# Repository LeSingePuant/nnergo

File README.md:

# nnErgo
nnErgo - NiceNano Ergonomic Keypad

This is a PCB I am using to learn KiCad design. It is designed simply for my needs. Any of my designs are able to be used, remixed, redone, produced commercially or otherwise as long as an attribution of my username "LeSingePuant" is given as credit (and a PM via Reddit or Twitter would be nice, although I rarely use Twitter). Thank you.

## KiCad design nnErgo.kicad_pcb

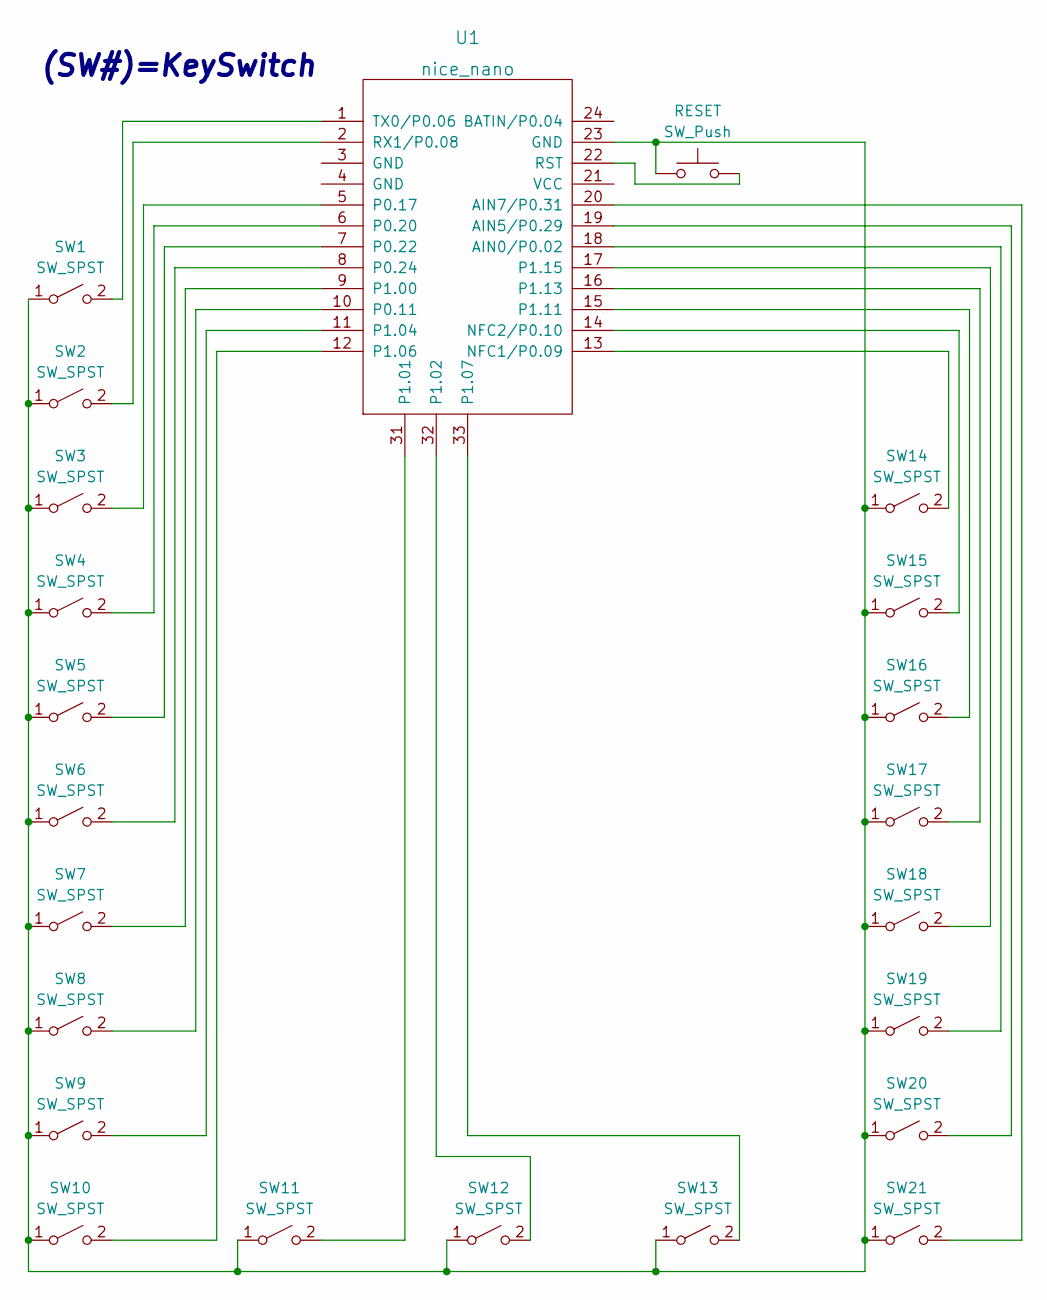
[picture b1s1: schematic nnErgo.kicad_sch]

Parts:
RESET: SW_Push; SW_PUSH_6mm
SW1, SW2, SW3, SW4, SW5, SW6, SW7, SW8, SW9, SW10, SW11, SW12, SW13, SW14, SW15, SW16, SW17, SW18, SW19, SW20, SW21: SW_SPST; Kailh_socket_MX
U1: nice_nano

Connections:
unnamed 0: RESET.1, SW1.1 (A), SW2.1 (A), SW3.1 (A), SW4.1 (A), SW5.1 (A), SW6.1 (A), SW7.1 (A), SW8.1 (A), SW9.1 (A), SW10.1 (A), SW11.1 (A), SW12.1 (A), SW13.1 (A), SW14.1 (A), SW15.1 (A), SW16.1 (A), SW17.1 (A), SW18.1 (A), SW19.1 (A), SW20.1 (A), SW21.1 (A), U1.23 (GND); also elsewhere on the board
unnamed: SW1.2 (B), U1.1 (TX0/P0.06)
unnamed: SW2.2 (B), U1.2 (RX1/P0.08)
unnamed: SW3.2 (B), U1.5 (P0.17)
unnamed: SW4.2 (B), U1.6 (P0.20)
unnamed: SW5.2 (B), U1.7 (P0.22)
unnamed: SW6.2 (B), U1.8 (P0.24)
unnamed: SW7.2 (B), U1.9 (P1.00)
unnamed: SW8.2 (B), U1.10 (P0.11)
unnamed: SW9.2 (B), U1.11 (P1.04)
unnamed: SW10.2 (B), U1.12 (P1.06)
unnamed: SW11.2 (B), U1.31 (P1.01)
unnamed: SW12.2 (B), U1.32 (P1.02)
unnamed: SW13.2 (B), U1.33 (P1.07)
unnamed: SW14.2 (B), U1.13 (NFC1/P0.09)
unnamed: SW15.2 (B), U1.14 (NFC2/P0.10)
unnamed: SW16.2 (B), U1.15 (P1.11)
unnamed: SW17.2 (B), U1.16 (P1.13)
unnamed: SW18.2 (B), U1.17 (P1.15)
unnamed: SW19.2 (B), U1.18 (AIN0/P0.02)
unnamed: SW20.2 (B), U1.19 (AIN5/P0.29)
unnamed: SW21.2 (B), U1.20 (AIN7/P0.31)
unnamed 22: RESET.2, U1.22 (RST); also elsewhere on the board

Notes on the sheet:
(SW#)=KeySwitch

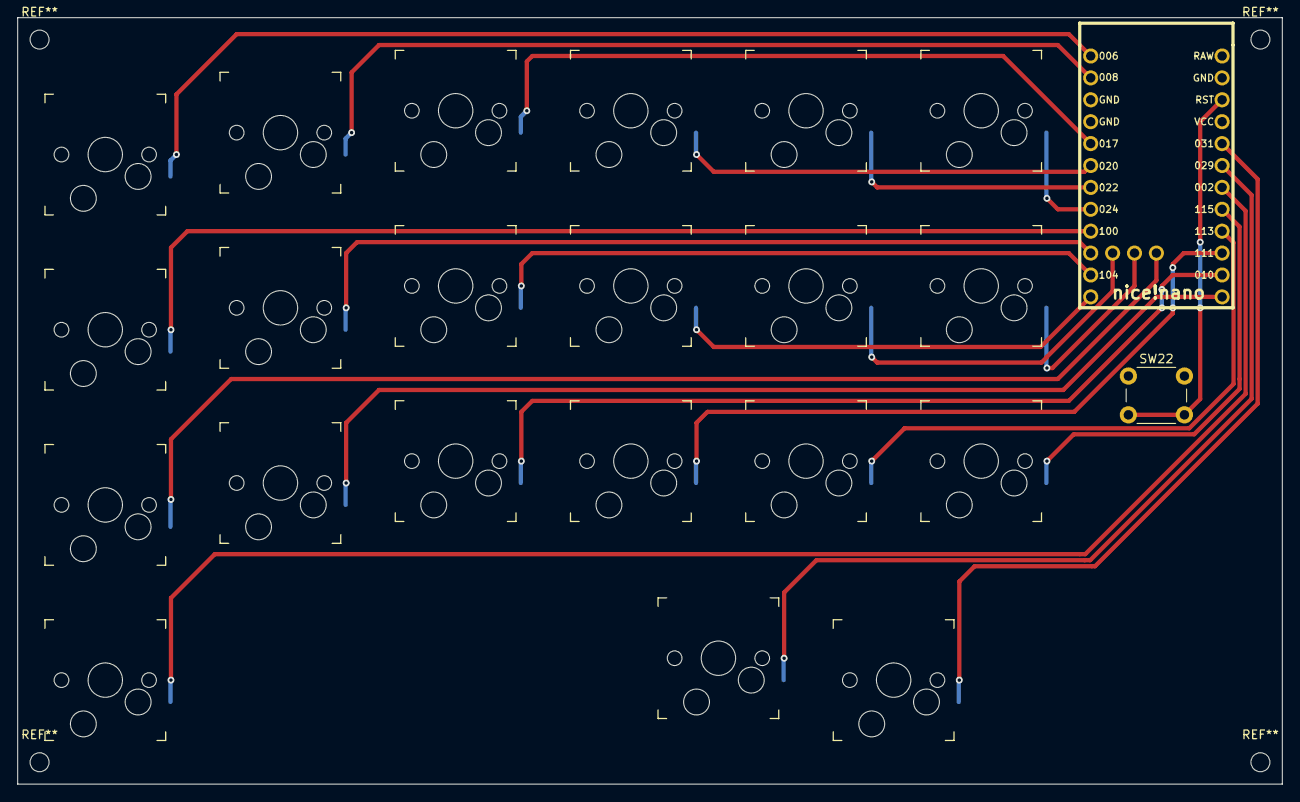
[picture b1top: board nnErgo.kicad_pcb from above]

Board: 2 copper layers, 146.7 x 88.9 mm, 23 parts (0 on the bottom side), 23 nets.

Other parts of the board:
SW22: SW_Push; SW_PUSH_6mm

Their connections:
unnamed 0: SW22.1; also elsewhere on the board
unnamed 22: SW22.2; also elsewhere on the board
